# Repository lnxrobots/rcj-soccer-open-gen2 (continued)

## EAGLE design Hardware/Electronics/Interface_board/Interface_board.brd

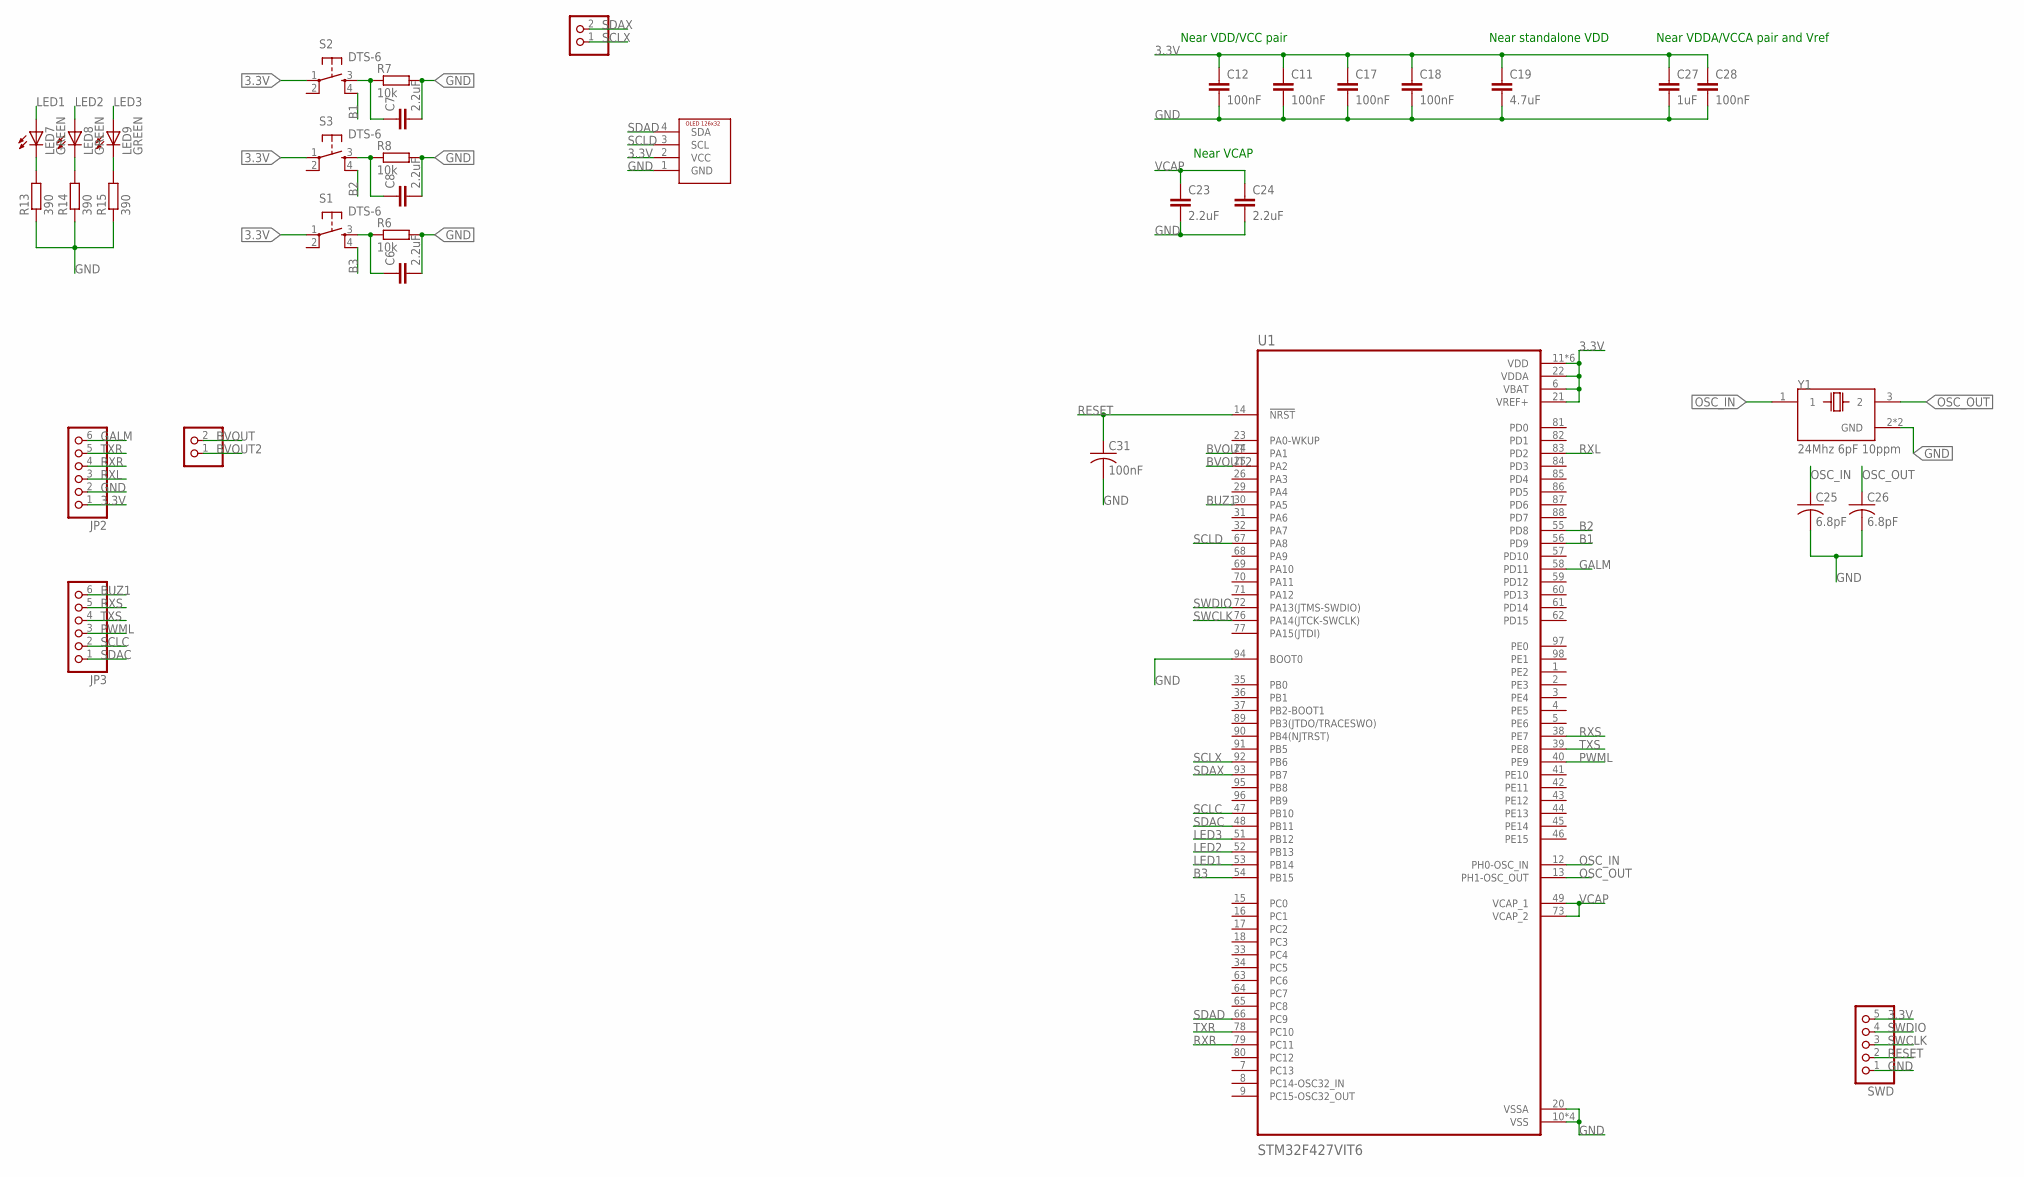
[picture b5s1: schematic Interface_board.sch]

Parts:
C6, C7, C8, C23, C24: 2.2uF; C0603
C11, C12, C17, C18, C28, C31: 100nF; C0603
C19: 4.7uF; C0603
C25, C26: 6.8pF; C0603
C27: 1uF; C0603
JP1, JP4: PINHD-1X2; 1X02
JP2, JP3: PINHD-1X6; 1X06
LED7, LED8, LED9: GREEN; CHIPLED_0603
R6, R7, R8: 10k; R0603
R13, R14, R15: 390; R0603
S1, S2, S3: DTS-6
SWD: PINHD-1X5/90; 1X05/90
U1: STM32F427VIT6; QFP50P1600X1600X160-100N
U$1: OLED126X32THROUGH_HOLE; OLED128X64
Y1: 24Mhz 6pF 10ppm; XTAL_TSX-3225_16.0000MF18X-AC3

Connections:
3.3V: C11.1, C12.1, C17.1, C18.1, C19.1, C27.1, C28.1, JP2.1, S1.1, S2.1, S3.1, SWD.5, U1.6 (VBAT), U1.11 (VDD), U1.19 (VDD), U1.21 (VREF+), U1.22 (VDDA), U1.28 (VDD), U1.50 (VDD), U1.75 (VDD), U1.100 (VDD), U$1.2 (VCC)
B1: S2.4, U1.56 (PD9)
B2: S3.4, U1.55 (PD8)
B3: S1.4, U1.54 (PB15)
BUZ1: JP3.6, U1.30 (PA5)
BVOUT: JP4.2, U1.24 (PA1)
BVOUT2: JP4.1, U1.25 (PA2)
GALM: JP2.6, U1.58 (PD11)
GND: C6.2, C7.2, C8.2, C11.2, C12.2, C17.2, C18.2, C19.2, C23.2, C24.2, C25.2, C26.2, C27.2, C28.2, C31.2, JP2.2, R6.2, R7.2, R8.2, R13.1, R14.1, R15.1, SWD.1, U1.10 (VSS), U1.20 (VSSA), U1.27 (VSS), U1.74 (VSS), U1.94 (BOOT0), U1.99 (VSS), U$1.1 (GND), Y1.2 (GND), Y1.4 (GND)
LED1: LED7.A, U1.53 (PB14)
LED2: LED8.A, U1.52 (PB13)
LED3: LED9.A, U1.51 (PB12)
unnamed: C6.1, R6.1, S1.3
unnamed: C7.1, R7.1, S2.3
unnamed: C8.1, R8.1, S3.3
unnamed: LED7.C, R13.2
unnamed: LED8.C, R14.2
unnamed: LED9.C, R15.2
OSC_IN: C25.1, U1.12 (PH0-OSC_IN), Y1.1
OSC_OUT: C26.1, U1.13 (PH1-OSC_OUT), Y1.3 (2)
PWML: JP3.3, U1.40 (PE9)
RESET: C31.1, SWD.2, U1.14 (!NRST)
RXL: JP2.3, U1.83 (PD2)
RXR: JP2.4, U1.79 (PC11)
RXS: JP3.5, U1.38 (PE7)
SCLC: JP3.2, U1.47 (PB10)
SCLD: U1.67 (PA8), U$1.3 (SCL)
SCLX: JP1.1, U1.92 (PB6)
SDAC: JP3.1, U1.48 (PB11)
SDAD: U1.66 (PC9), U$1.4 (SDA)
SDAX: JP1.2, U1.93 (PB7)
SWCLK: SWD.3, U1.76 (PA14(JTCK-SWCLK))
SWDIO: SWD.4, U1.72 (PA13(JTMS-SWDIO))
TXR: JP2.5, U1.78 (PC10)
TXS: JP3.4, U1.39 (PE8)
VCAP: C23.1, C24.1, U1.49 (VCAP_1), U1.73 (VCAP_2)

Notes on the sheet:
Near VDD/VCC pair
Near VDDA/VCCA pair and Vref
Near VCAP
Near standalone VDD

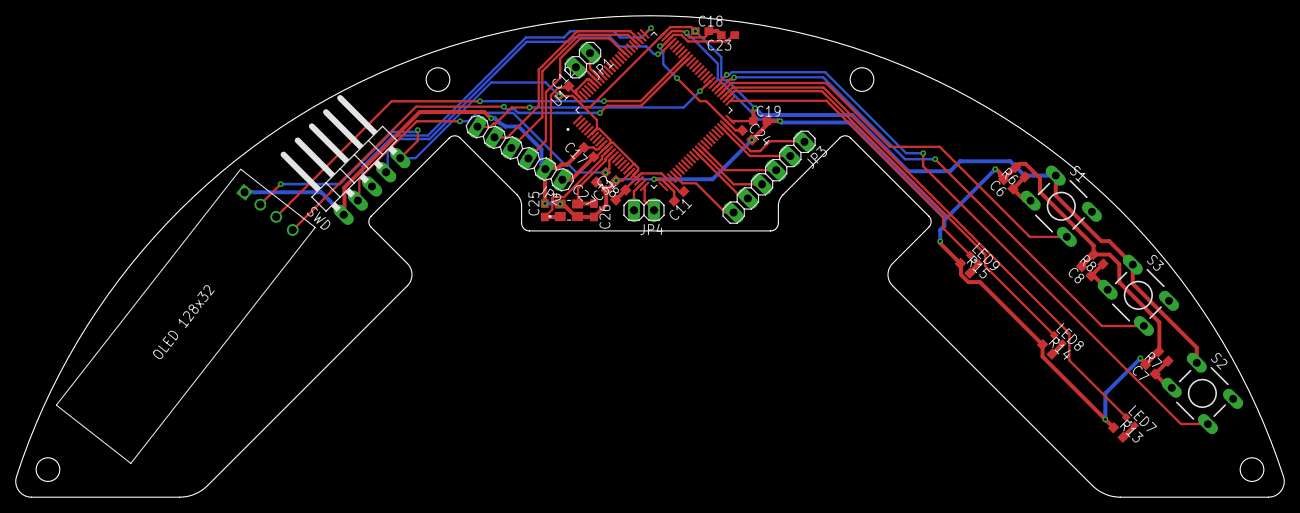
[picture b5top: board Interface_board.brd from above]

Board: 2 copper layers, 161.0 x 61.1 mm, 35 parts (0 on the bottom side), 36 nets.

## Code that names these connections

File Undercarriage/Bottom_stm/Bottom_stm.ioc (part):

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Mcu.Name=STM32G474R(B-C-E)Tx
Mcu.Package=LQFP64
Mcu.UserName=STM32G474RETx
PA0.Mode=IN1-Single-Ended
PA0.Signal=ADC1_IN1
PA1.Mode=IN2-Single-Ended
PA1.Signal=ADC2_IN2
PA10.GPIOParameters=GPIO_Label
PA10.GPIO_Label=M4_CCWE
PA10.Signal=GPIO_Output
PA11.Mode=Output_TB2
PA11.Signal=HRTIM1_CHB2
PA12.GPIOParameters=GPIO_Label
PA12.GPIO_Label=M4_CWE
PA12.Signal=GPIO_Output
PA13.Mode=Serial_Wire
PA13.Signal=SYS_JTMS-SWDIO
PA14.Mode=Serial_Wire
PA14.Signal=SYS_JTCK-SWCLK
PA15.GPIOParameters=GPIO_Label
PA15.GPIO_Label=KICK
PA15.Signal=GPIO_Output
PA4.GPIOParameters=GPIO_Label
PA4.GPIO_Label=GPIO_LED
PA4.Signal=GPIO_Output
PA6.Mode=IN3-Single-Ended
PA6.Signal=ADC2_IN3
PA7.Mode=IN4-Single-Ended
PA7.Signal=ADC2_IN4
PA8.Mode=IN1-Single-Ended
PA8.Signal=ADC5_IN1
PA9.Mode=IN2-Single-Ended
PA9.Signal=ADC5_IN2
PB0.Mode=IN12-Single-Ended
PB0.Signal=ADC3_IN12
PB1.Mode=IN1-Single-Ended
PB1.Signal=ADC3_IN1
PB12.Mode=IN3-Single-Ended
PB12.Signal=ADC4_IN3
PB13.Mode=IN5-Single-Ended
PB13.Signal=ADC3_IN5
PB14.Mode=IN5-Single-Ended
PB14.Signal=ADC1_IN5
PB15.Mode=IN5-Single-Ended
PB15.Signal=ADC4_IN5
PB2.GPIOParameters=GPIO_Label
PB2.GPIO_Label=M2_TIM
PB2.Signal=S_TIM20_CH1
PB4.GPIOParameters=GPIO_Label
PB4.GPIO_Label=MD_TIM
PB4.Signal=S_TIM16_CH1
PB5.GPIOParameters=GPIO_Label
PB5.GPIO_Label=MD_CWE
PB5.Signal=GPIO_Output
PB6.GPIOParameters=GPIO_Label
PB6.GPIO_Label=MD_CCWE
PB6.Signal=GPIO_Output
PC0.GPIOParameters=GPIO_Label
PC0.GPIO_Label=M1_TIM
PC0.Signal=S_TIM1_CH1
PC1.GPIOParameters=GPIO_Label
PC1.GPIO_Label=M1_CWE
PC1.Signal=GPIO_Output
PC10.Mode=Asynchronous
PC10.Signal=UART4_TX
PC11.Mode=Asynchronous
PC11.Signal=UART4_RX
PC2.GPIOParameters=GPIO_Label
PC2.GPIO_Label=M1_CCWE
PC2.Signal=GPIO_Output
PC4.GPIOParameters=GPIO_Label
PC4.GPIO_Label=M2_CWE
PC4.Signal=GPIO_Output
PC5.GPIOParameters=GPIO_Label
PC5.GPIO_Label=M2_CCWE
PC5.Signal=GPIO_Output
PC6.Signal=S_TIM8_CH1
PC7.GPIOParameters=GPIO_Label
PC7.GPIO_Label=M3_CCWE
PC7.Signal=GPIO_Output
PC8.GPIOParameters=GPIO_Label
PC8.GPIO_Label=M3_CWE
PC8.Signal=GPIO_Output
PF0-OSC_IN.Mode=HSE-External-Oscillator
PF0-OSC_IN.Signal=RCC_OSC_IN
PF1-OSC_OUT.Mode=HSE-External-Oscillator
PF1-OSC_OUT.Signal=RCC_OSC_OUT
RCC.HSE_VALUE=24000000
RCC.SYSCLKFreq_VALUE=170000000
RCC.SYSCLKSource=RCC_SYSCLKSOURCE_PLLCLK
board=custom

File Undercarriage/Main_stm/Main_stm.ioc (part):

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Mcu.Name=STM32F427V(G-I)Tx
Mcu.Package=LQFP100
Mcu.UserName=STM32F427VITx
PA1.GPIOParameters=GPIO_Label
PA1.GPIO_Label=BVIN
PA1.Signal=ADCx_IN1
PA13.Mode=Serial_Wire
PA13.Signal=SYS_JTMS-SWDIO
PA14.Mode=Serial_Wire
PA14.Signal=SYS_JTCK-SWCLK
PA2.GPIOParameters=GPIO_Label
PA2.GPIO_Label=BVIN2
PA2.Signal=ADCx_IN2
PA5.GPIOParameters=GPIO_Label
PA5.GPIO_Label=BUZ_TIM
PA5.Signal=S_TIM2_CH1_ETR
PA8.Mode=I2C
PA8.Signal=I2C3_SCL
PB10.Mode=Asynchronous
PB10.Signal=USART3_TX
PB11.Mode=Asynchronous
PB11.Signal=USART3_RX
PB12.GPIOParameters=GPIO_Label
PB12.GPIO_Label=L3
PB12.Signal=GPIO_Output
PB13.GPIOParameters=GPIO_Label
PB13.GPIO_Label=L2
PB13.Signal=GPIO_Output
PB14.GPIOParameters=GPIO_Label
PB14.GPIO_Label=L1
PB14.Signal=GPIO_Output
PB15.GPIOParameters=GPIO_Label
PB15.GPIO_Label=B3
PB15.Signal=GPIO_Input
PC10.Mode=Asynchronous
PC10.Signal=UART4_TX
PC11.Mode=Asynchronous
PC11.Signal=UART4_RX
PC12.Mode=Asynchronous
PC12.Signal=UART5_TX
PC9.Mode=I2C
PC9.Signal=I2C3_SDA
PD11.GPIOParameters=GPIO_Label
PD11.GPIO_Label=GAL_M
PD11.Signal=GPIO_Input
PD2.Mode=Asynchronous
PD2.Signal=UART5_RX
PD8.GPIOParameters=GPIO_Label
PD8.GPIO_Label=B2
PD8.Signal=GPIO_Input
PD9.GPIOParameters=GPIO_Label
PD9.GPIO_Label=B1
PD9.Signal=GPIO_Input
PE7.Mode=Asynchronous
PE7.Signal=UART7_RX
PE8.Mode=Asynchronous
PE8.Signal=UART7_TX
PE9.Signal=S_TIM1_CH1
PH0/OSC_IN.Mode=HSE-External-Oscillator
PH0/OSC_IN.Signal=RCC_OSC_IN
PH1/OSC_OUT.Mode=HSE-External-Oscillator
PH1/OSC_OUT.Signal=RCC_OSC_OUT
RCC.HSE_VALUE=25000000
RCC.SYSCLKFreq_VALUE=180000000
RCC.SYSCLKSource=RCC_SYSCLKSOURCE_PLLCLK
board=custom

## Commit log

2024-06-17 Add RoboCup Europe 2024 code
2024-06-17 Maybe fix github linguist
